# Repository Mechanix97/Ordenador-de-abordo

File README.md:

# Motorcycle On-Board Computer

A digital instrument cluster for a **Zanella RX 150** motorcycle that replaces the original analog
gauges. It measures **speed, engine RPM, fuel level and GPS position** and shows them on two OLED
displays, together with two LED bar graphs that can be read at a glance while riding.

Built on an STM32F103 "Blue Pill" with the STM32Cube HAL, on two home-made PCBs (toner transfer)
designed in KiCad to fit inside the original dashboard housing.

> Final project for *Seminario de Sistemas Embebidos*, Facultad de Ingeniería, Universidad de Buenos
> Aires (FIUBA), developed between November 2020 and March 2021. The project is being revived:
> see the [open issues](https://github.com/Mechanix97/Ordenador-de-abordo/issues) for the roadmap.

## Features

| Measurement | How it works | Status |
|---|---|---|
| Speed | Wheel switch → external interrupt, pulse counter | Shows raw pulse count ([#5](../../issues/5)) |
| Engine RPM | Rectified ignition signal → RC filter + Zener → ADC | Raw ADC value, uncalibrated ([#6](../../issues/6)) |
| Fuel level | Tank float sender (8–100 Ω) in a resistive divider → ADC | Raw ADC value ([#6](../../issues/6)) |
| GPS position, date, time | u-blox NEO-6M over UART + DMA, `$GPRMC` parsing | Working, accuracy < 10 m; known parser bugs ([#1](../../issues/1)–[#3](../../issues/3)) |
| LED bar graphs | 2 × LM3915 driven by filtered PWM, 10 LEDs each | Hardware works; firmware keeps them off |
| Push button | External interrupt | Counter only ([#7](../../issues/7)) |
| Bluetooth | HC-05 on USART1 | Used for debug output |

Display layout:

- **SH1106 (1.3")**: `VEL` (speed), `RPM`, `GAS` (fuel).
- **SSD1306 (0.96")**: `BUT` (button counter), `LAT`, `LON`, `DAT` (date), `TIME` (UTC-3).

## Hardware

### Components

| Component | Part | Interface |
|---|---|---|
| Microcontroller | STM32F103 "Blue Pill" (Cortex-M3, 72 MHz) | — |
| Display 1 | SH1106 128×64 OLED, 1.3" (I2C address `0x78`) | I2C1 |
| Display 2 | SSD1306 128×64 OLED, 0.96" (I2C address `0x7A`) | I2C1 |
| LED bar graphs | 2 × LM3915 + 20 LEDs | TIM2 PWM |
| GPS | u-blox NEO-6M module | USART3, 9600 baud |
| Bluetooth | HC-05 module | USART1, 9600 baud |

The project targets the `STM32F103CBTx` (128 KB flash). The firmware is about 24 KB, so it also fits
the more common STM32F103C8 (64 KB) found on most Blue Pill boards.

### Pinout

| Pin | Function | Peripheral |
|---|---|---|
| PA0 | Push button | EXTI0, rising edge, pull-up |
| PA1 | LED bar graph 2 | TIM2_CH2 PWM |
| PA2 | LED bar graph 1 | TIM2_CH3 PWM |
| PA6 | Engine RPM | ADC1_IN6 |
| PA7 | Fuel level | ADC2_IN7 |
| PA8 | Wheel-speed sensor | EXTI8, rising edge, pull-down |
| PA9 / PA10 | HC-05 Bluetooth TX / RX | USART1 |
| PB8 / PB9 | OLED SCL / SDA | I2C1 (remapped), 400 kHz |
| PB10 / PB11 | GPS TX / RX | USART3, RX via DMA |
| PA13 / PA14 | SWDIO / SWCLK | Debug |

The full configuration lives in [`Ordenador-abordo.ioc`](Ordenador-abordo.ioc) (STM32CubeMX).

### Sensor interfaces

| Fuel level | Engine RPM |
|---|---|
|  |  |
| The float sender goes from 100 Ω (reserve) to 8 Ω (full). With a 100 Ω pull-up the ADC reads roughly 100–2048 out of 4095. | The ignition signal is rectified, divided and filtered; a 5.5 V Zener protects the ADC pin from ignition spikes. The reading grows with RPM but is not calibrated yet. |

The speed sensor is a simple switch that closes once per wheel revolution.

### PCBs

Two boards, designed in KiCad 5.1 ([`Kicad/`](Kicad)) and made at home by toner transfer.

| Control board (100 × 50 mm) | Display board |
|---|---|
|  |  |
| Blue Pill carrier, Wago terminal blocks for the bike harness, signal conditioning, headers for the GPS and Bluetooth modules. | Shaped to fit the original gauge housing: two arcs of 10 LEDs driven by LM3915s, and headers for both OLED displays. |

> The `.sch` schematic files are empty; only the PCB layouts exist. Rebuilding the schematics is
> tracked in [#15](../../issues/15).

## Building

### Requirements

- [Arm GNU Toolchain](https://developer.arm.com/downloads/-/arm-gnu-toolchain-downloads) (`arm-none-eabi-gcc`)
- GNU Make
- [stlink-tools](https://github.com/stlink-org/stlink) (`st-flash`) and an ST-Link V2 for flashing

**Ubuntu / Debian**

```sh
sudo apt-get install build-essential gcc-arm-none-eabi libnewlib-arm-none-eabi stlink-tools
```

**Windows**: install [STM32CubeCLT](https://www.st.com/en/development-tools/stm32cubeclt.html) (includes
the toolchain) and GNU Make (e.g. `choco install make`). If the toolchain is not on `PATH`, pass it
explicitly: `make GCC_PATH="C:/ST/STM32CubeCLT_x.y.z/GNU-tools-for-STM32/bin"`.

### Commands

```sh
make all     # build build/Ordenador-abordo.{elf,hex,bin}
make clean   # remove build/
make erase   # erase the MCU flash
make flash   # write build/Ordenador-abordo.bin at 0x08000000
```

Connect the ST-Link to the SWD header of the Blue Pill (3.3V, SWDIO, SWCLK, GND).

Every push and pull request is built by [GitHub Actions](.github/workflows/build.yml); the
`.elf`/`.hex`/`.bin` files can be downloaded from the run's artifacts.

## Repository layout

```
Core/            Application code (app.c, gps.c, rpm.c, gas.c), OLED drivers, CubeMX-generated init code
Drivers/         STM32F1 HAL and CMSIS (vendor code, do not edit)
Kicad/           PCB designs: Placa-control (control board) and Placa-pantallas (display board)
docs/images/     Images used in this README
Makefile         Build script (generated by CubeMX, extended with flash/erase targets)
Ordenador-abordo.ioc   STM32CubeMX project
AGENTS.md        Guidelines for AI coding agents working on this repo
```

## Roadmap

Planned improvements are tracked as [GitHub issues](https://github.com/Mechanix97/Ordenador-de-abordo/issues), including:

- Robust GPS reception and NMEA parsing, timezone fixes ([#1](../../issues/1)–[#4](../../issues/4))
- Real speed in km/h, odometer and trip meter ([#5](../../issues/5))
- Calibrated RPM and fuel readings, driving the LED bar graphs ([#6](../../issues/6))
- Watchdog and robustness for an automotive environment ([#11](../../issues/11))
- Host-side unit tests ([#16](../../issues/16)) and KiCad schematics, Gerbers and BOM ([#15](../../issues/15))
- A 3D-printed enclosure and GPS navigation features

## License

No license has been chosen yet ([#18](../../issues/18)). Note that the OLED drivers in `Core/` are
GPL-3.0 and the ST HAL/CMSIS in `Drivers/` are BSD-3-Clause / Apache-2.0.

## Author

Lucas Alexis Rack ([@Mechanix97](https://github.com/Mechanix97))

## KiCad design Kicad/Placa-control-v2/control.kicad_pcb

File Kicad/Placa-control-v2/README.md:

# Control board v2

Redesign of the control board (`Kicad/Placa-control`) focused on **not destroying the electronics
again**. The v1 board was killed through the RPM input, which was wired straight from the ignition
coil to the microcontroller.

- **Single-sided, through-hole only**, for home etching (toner transfer). 3 wire jumpers.
- Same outline as v1 (100 × 50 mm with the chamfered corner), so it fits the original dashboard housing.
- KiCad 10 project with a **complete schematic**: v1 only had a PCB.
- ERC and DRC are clean and run in CI on every change (`.github/workflows/kicad.yml`).

| | |
|---|---|
| Schematic | [docs/control-v2-schematic.pdf](docs/control-v2-schematic.pdf) |
| Layout (copper + silkscreen, seen from the component side) | [docs/control-v2-layout.svg](docs/control-v2-layout.svg) |
| Gerbers, drill file, BOM, toner-transfer PDF | CI artifact `control-board-fab-<sha>` of the **KiCad** workflow |

## Why v1 failed

1. **RPM input.** Coil → diode → 100 kΩ → 100 kΩ ∥ 100 nF ∥ **5.5 V Zener** → PA6.
   - PA6 is a 3.3 V pin, not 5 V tolerant: its absolute maximum is about 3.6 V. The MCU's internal
     protection diodes conducted before the Zener did, and every spark injected current into the
     3.3 V rail.
   - That rail also feeds the displays, the GPS and the Bluetooth module, which is why everything
     died at once.
   - A single small 0204 resistor also had to stand hundreds of volts.
2. **Footprint bug.** One row of the v1 Blue Pill footprint was numbered in reverse. 5 V, GND and the
   RPM signal landed on the wrong module pins and had to be fixed with wires.
3. **No protection on the 12 V input or on the sensor inputs**, and no protection against a
   failing or mis-adjusted regulator preset.

## What's new

| Block | v2 circuit | Protects against |
|---|---|---|
| RPM input | 1N4007 → 3 × 47 kΩ in series → **PC817 optocoupler** (+ 1N4148 across the LED). Output to PA6 through 1 kΩ, 1 nF filter, internal pull-up | Coil voltage never reaches the MCU (galvanic isolation through the opto); negative pulses; resistor over-voltage |
| | 2.5 mm clearance from the coil nets to everything else (custom DRC rule, applied to the GND pour too); empty connector pins on both sides of the coil input | Arcing and creepage |
| 12 V input | PTC fuse 0.5 A / 60 V → 1N5819 (reverse polarity) → P6KE22A TVS + 47 µF | Shorts, reversed battery, load-dump spikes (clamped to ~31 V, below the 40 V limit of LM2596 modules) |
| 5 V rail | PTC fuse 0.5 A → **1N5340B 6 V / 5 W Zener crowbar** + 100 µF | A failed or mis-adjusted regulator preset: the Zener conducts and the PTC trips instead of 12 V reaching the modules |
| Wheel speed (PA8) | 4.7 kΩ pull-up to 5 V (switch to GND), 10 kΩ series, 100 nF, 4.7 V Zener | Shorts to 12 V, spikes, contact bounce |
| Fuel level (PA7) | 5 V → 1N4148 → 150 Ω divider with the sender, 10 kΩ series, 100 nF, 3.3 V Zener | Sender wire touching 12 V (no back-feed into 5 V), spikes |
| Button (PA0) | 1 kΩ series + 100 nF (internal pull-up) | ESD, bounce |
| LED bars | 10 kΩ / 8.2 kΩ / 1 µF PWM filters (full scale ≈ 1.5 V for the LM3915) | — |

## Connectors

| Ref | Type | Pin 1 → n |
|---|---|---|
| J1 POWER | Wago 734-135 (5 pins) | 1 +12 V (after the ignition switch), 2 GND, 3 to regulator IN+, 4 regulator GND (IN− / OUT−), 5 from regulator OUT+ |
| J2 SENSORS | Wago **734-136 (6 pins)** | 1 fuel sender, 2 *empty*, 3 **ignition coil**, 4 *empty*, 5 wheel switch, 6 GND |
| J3 DISPLAYS | 1×4 socket | 1 GND, 2 +5 V, 3 SDA (PB9), 4 SCL (PB8) |
| J7 LED BARS | 1×3 socket | 1 BAR1 (PA2), 2 GND, 3 BAR2 (PA1) |
| J4 GPS | 1×4 socket | 1 GND, 2 TX → PB11, 3 RX ← PB10, 4 VCC (+5 V) |
| J5 BLUETOOTH | 1×6 socket | 1 EN (n.c.), 2 VCC (+5 V), 3 GND, 4 TXD → PA10, 5 RXD ← PA9, 6 STATE (n.c.) |
| J6 BUTTON | 1×2 socket | 1 button (to PA0), 2 GND |

- **Display board wiring changes.** The old 6-wire cable is replaced by J3 (OLEDs) and J7 (LM3915
  inputs), so the display board needs rewiring.
- **The RPM wire goes to the coil primary**, the low-voltage terminal driven by the CDI. Never connect
  it to the spark plug lead.
- **The external step-down module:** IN+ on J1-3, OUT+ on J1-5, and its common GND on J1-4.
  **Adjust it to 5.0 V before connecting it.**

## Wire jumpers

The board is single-sided, so three crossings are made with insulated wire on the component side.
They are drawn on the silkscreen as `W1`–`W3`:

| Ref | Net | Where |
|---|---|---|
| W1 | +5V | Long diagonal on the left of the Blue Pill (feeds the module, displays and Bluetooth) |
| W2 | GND | Short, above the left end of the Blue Pill |
| W3 | GND | **Under the Blue Pill** (between the two socket rows): install it before the sockets |

## Assembly notes

- Parts under the Blue Pill must be lower than ~7 mm. Only W3 is there; use standard 8.5 mm female headers.
- The `BluePill_Socketed` footprint prints the pin names next to each pad. **Compare them with the
  labels on your module before soldering the headers.** USB goes towards the right edge, SWD towards
  the left.
- R1–R3: use 1/4 W metal-film resistors (≥ 250 V). The PTCs are 5.1 mm radial, rated 60 V (RXEF050,
  MF-R050 or similar).
- Wago 734 pins are 1 mm square: drill the J1/J2 holes with 1.3–1.5 mm.
- A conformal coating (or clear nail polish) over the RPM area improves creepage in a damp environment.

## Bring-up checklist

1. Without the Blue Pill or any module plugged in, power J1-1 from a bench supply (12 V,
   current-limited to ~200 mA). Check about 11.6 V on J1-3 (regulator input).
2. Connect the step-down module and check **5.0 V** on J3-2 / J4-4 / J5-2.
3. Plug the Blue Pill, then the displays, GPS and Bluetooth one at a time.
4. On the bike, check the RPM input with the engine at idle: PA6 should show clean low pulses.
   A scope is ideal.

## Firmware

The pins are the same as v1, but some inputs work differently. The firmware and the `.ioc` are
already set up for this board:

| Pin | Board v2 behaviour | Firmware |
|---|---|---|
| PA6 (RPM) | Digital pulse from the optocoupler, low on every spark | TIM3_CH1 input capture (100 kHz, falling edge, internal pull-up, digital filter). `rpm.c` ignores edges closer than 2 ms (ignition ringing) and reports 0 after 500 ms without sparks. Set `RPM_SPARKS_PER_2_REV` in `rpm.h` for your CDI. |
| PA7 (fuel) | About 0.2 V (full) … 1.7 V (reserve), 10 kΩ source impedance | ADC2 with 239.5-cycle sampling. Calibrate `GAS_RAW_FULL` / `GAS_RAW_RESERVE` in `gas.h` with the raw value shown on the display. |
| PA8 (speed) | External pull-up, the switch pulls it low | No internal pull. |
| PA0 (button) | Internal pull-up | Unchanged. |

## Design rules

- Net classes are defined in `control.kicad_pro`:
  - **Default:** 0.6 mm tracks, 0.4 mm clearance.
  - **Power:** 1.0 mm tracks.
  - **HV:** the coil nets, 0.8 mm tracks.
- The 2.5 mm HV clearance is a custom rule in `control.kicad_dru`. It excludes the empty connector pins.
- The Blue Pill footprint declares its internally connected pins (GND 19/20/22, 3V3 18/21) as pad
  groups, so the DRC knows the module ties them together.
- The GND pour is part of the design. After editing, refill zones (`B`) before running the DRC.

## Fabrication

- **Toner transfer.** Print `control-copper-bottom.pdf` from the CI artifact **at 100 % scale and
  without mirroring**, and transfer it face-down onto the copper. Check the orientation with the
  Blue Pill footprint before etching.
- **Ordering the board.** The CI artifact also contains single-sided Gerbers and the Excellon drill file.

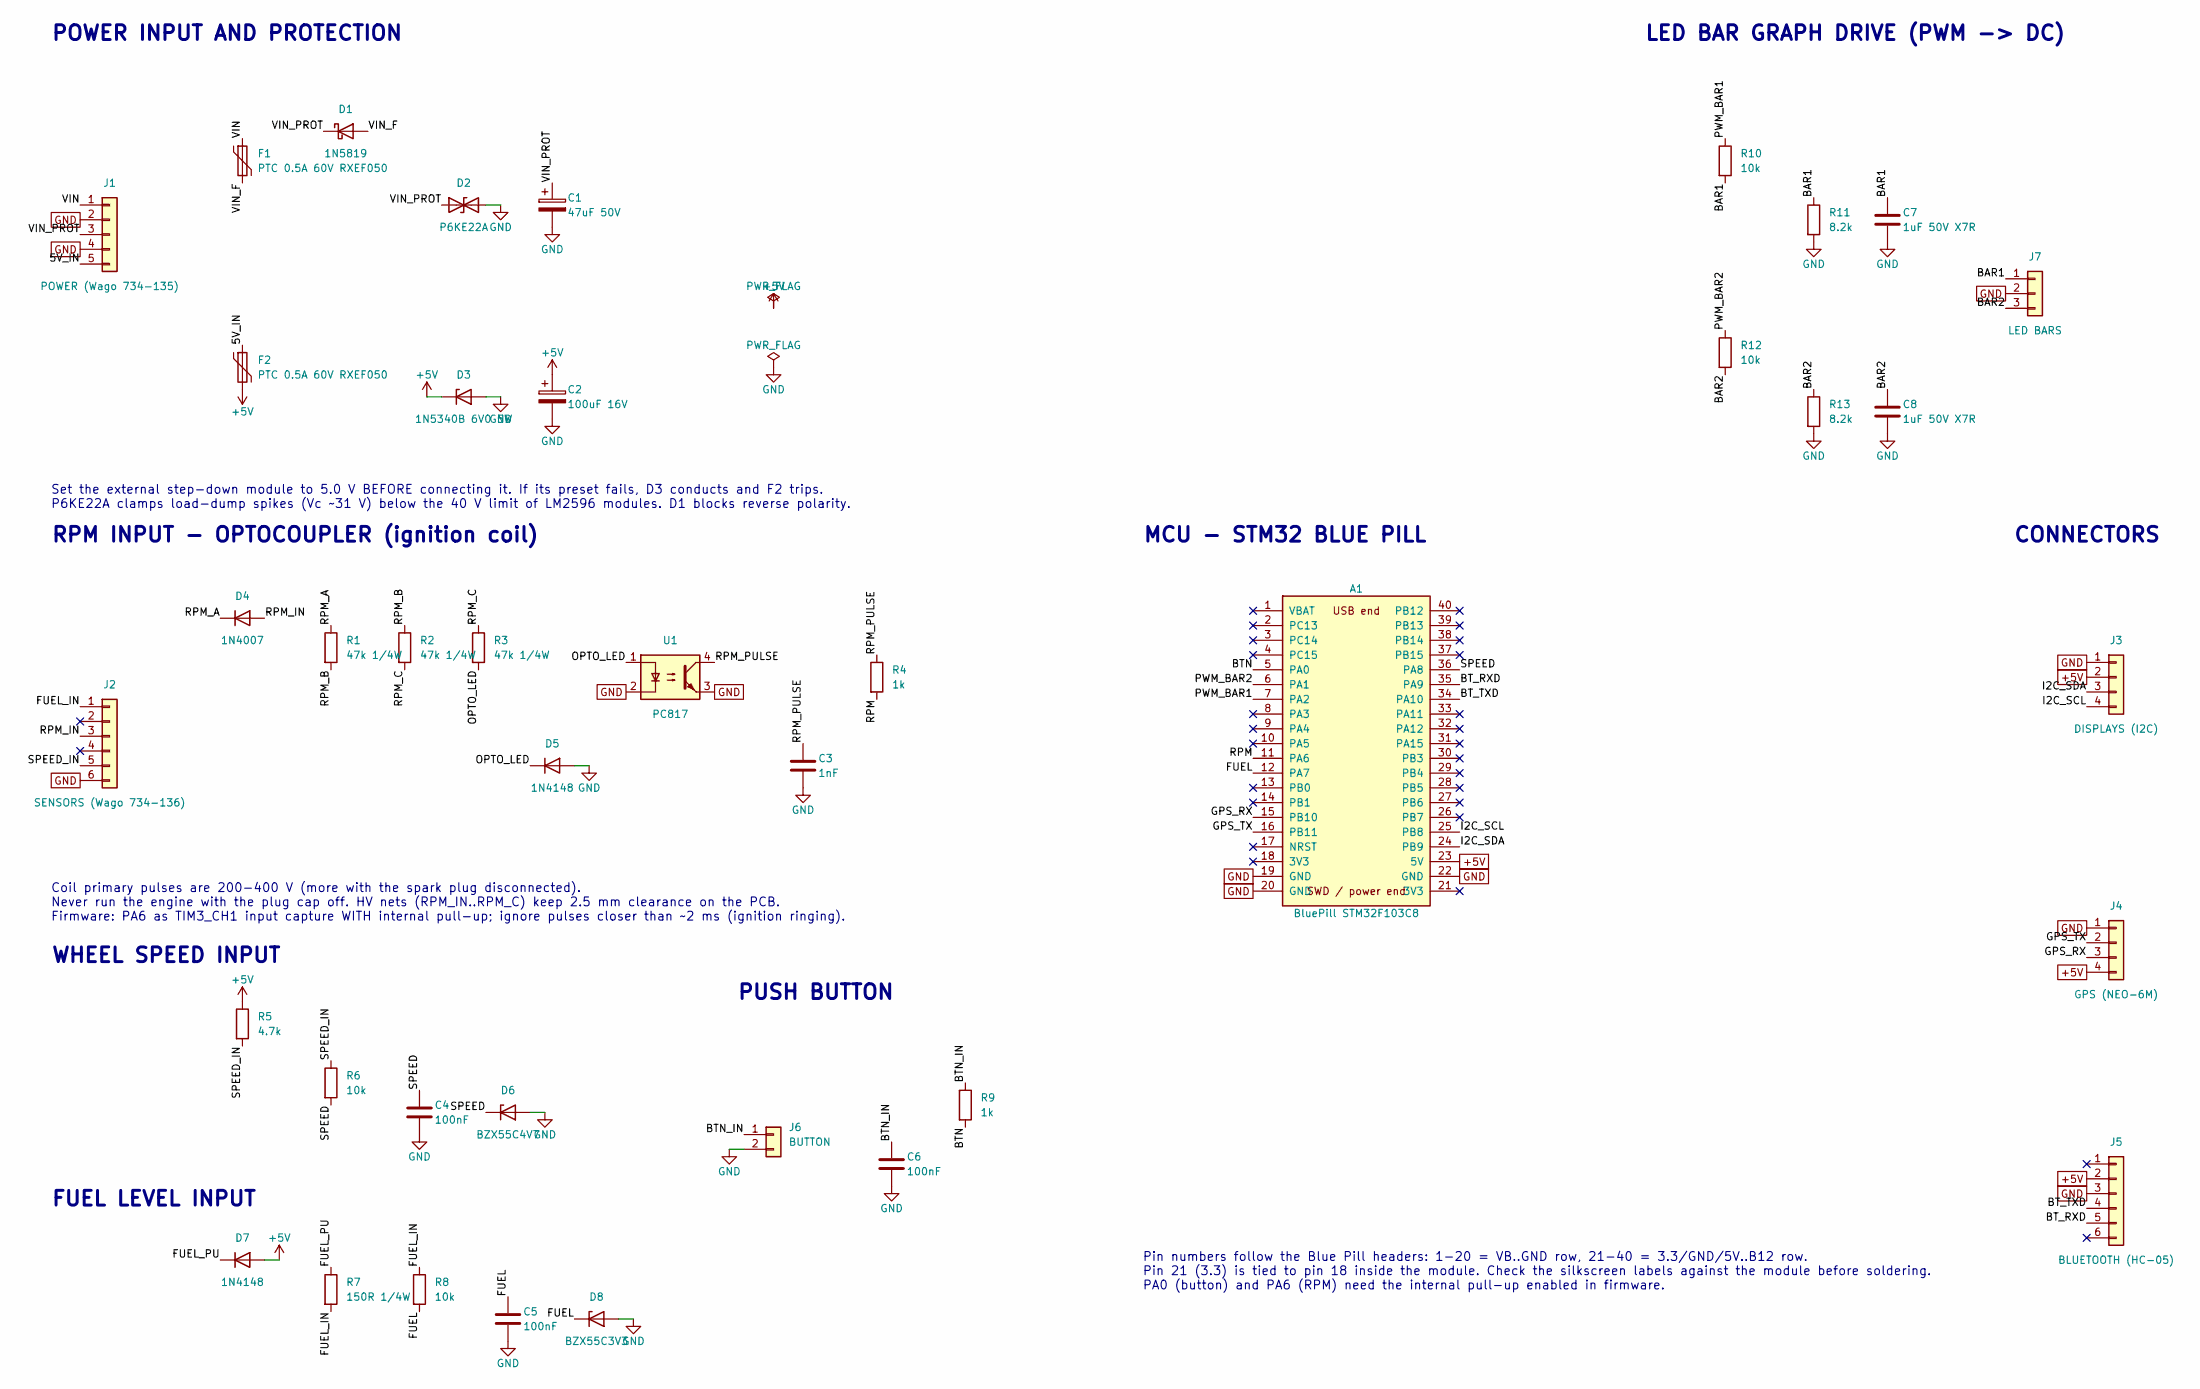
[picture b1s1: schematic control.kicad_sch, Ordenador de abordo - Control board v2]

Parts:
A1: BluePill STM32F103C8; BluePill_Socketed
C1: 47uF 50V; CP_Radial_D6.3mm_P2.50mm
C2: 100uF 16V; CP_Radial_D6.3mm_P2.50mm
C3: 1nF; C_Disc_D3.0mm_W1.6mm_P2.50mm
C4, C5, C6: 100nF; C_Disc_D3.0mm_W1.6mm_P2.50mm
C7, C8: 1uF 50V X7R; C_Disc_D3.0mm_W1.6mm_P2.50mm
D1: 1N5819; D_DO-41_SOD81_P10.16mm_Horizontal
D2: P6KE22A; D_DO-15_P10.16mm_Horizontal
D3: 1N5340B 6V0 5W; D_DO-201AE_P5.08mm_Vertical_AnodeUp
D4: 1N4007; D_DO-41_SOD81_P10.16mm_Horizontal
D5, D7: 1N4148; D_DO-35_SOD27_P2.54mm_Vertical_AnodeUp
D6: BZX55C4V7; D_DO-35_SOD27_P2.54mm_Vertical_AnodeUp
D8: BZX55C3V3; D_DO-35_SOD27_P2.54mm_Vertical_AnodeUp
F1, F2: PTC 0.5A 60V RXEF050; Fuse_Bourns_MF-RHT050
J1: POWER (Wago 734-135); Wago_734-135_1x05_P3.50mm_Vertical
J2: SENSORS (Wago 734-136); Wago_734-136_1x06_P3.50mm_Vertical
J3: DISPLAYS (I2C); PinSocket_1x04_P2.54mm_Vertical
J4: GPS (NEO-6M); PinSocket_1x04_P2.54mm_Vertical
J5: BLUETOOTH (HC-05); PinSocket_1x06_P2.54mm_Vertical
J6: BUTTON; PinSocket_1x02_P2.54mm_Vertical
J7: LED BARS; PinSocket_1x03_P2.54mm_Vertical
R1, R2, R3: 47k 1/4W; R_Axial_DIN0207_L6.3mm_D2.5mm_P10.16mm_Horizontal
R4, R9: 1k; R_Axial_DIN0207_L6.3mm_D2.5mm_P2.54mm_Vertical
R5: 4.7k; R_Axial_DIN0207_L6.3mm_D2.5mm_P2.54mm_Vertical
R6, R8, R10, R12: 10k; R_Axial_DIN0207_L6.3mm_D2.5mm_P2.54mm_Vertical
R7: 150R 1/4W; R_Axial_DIN0207_L6.3mm_D2.5mm_P2.54mm_Vertical
R11, R13: 8.2k; R_Axial_DIN0207_L6.3mm_D2.5mm_P2.54mm_Vertical
U1: PC817; DIP-4_W7.62mm

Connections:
+5V: A1.23 (5V), C2.1, D3.1 (K), D7.2 (A), F2.2, J3.2, J4.4, J5.2, R5.1; also elsewhere on the board
/5V_IN: F2.1, J1.5
/BAR1: C7.1, J7.1, R10.2, R11.1
/BAR2: C8.1, J7.3, R12.2, R13.1
/BTN: A1.5 (PA0), R9.2
/BTN_IN: C6.1, J6.1, R9.1
/BT_RXD: A1.35 (PA9), J5.5
/BT_TXD: A1.34 (PA10), J5.4
/FUEL: A1.12 (PA7), C5.1, D8.1 (K), R8.2
/FUEL_IN: J2.1, R7.2, R8.1
/FUEL_PU: D7.1 (K), R7.1
/GPS_RX: A1.15 (PB10), J4.3
/GPS_TX: A1.16 (PB11), J4.2
/I2C_SCL: A1.25 (PB8), J3.4
/I2C_SDA: A1.24 (PB9), J3.3
/OPTO_LED: D5.1 (K), R3.2, U1.1
/PWM_BAR1: A1.7 (PA2), R10.1
/PWM_BAR2: A1.6 (PA1), R12.1
/RPM: A1.11 (PA6), R4.2
/RPM_A: D4.1 (K), R1.1
/RPM_B: R1.2, R2.1
/RPM_C: R2.2, R3.1
/RPM_IN: D4.2 (A), J2.3
/RPM_PULSE: C3.1, R4.1, U1.4
/SPEED: A1.36 (PA8), C4.1, D6.1 (K), R6.2
/SPEED_IN: J2.5, R5.2, R6.1
/VIN: F1.1, J1.1
/VIN_F: D1.2 (A), F1.2
/VIN_PROT: C1.1, D1.1 (K), D2.1 (A1), J1.3
GND: A1.19 (GND), A1.20 (GND), A1.22 (GND), C1.2, C2.2, C3.2, C4.2, C5.2, C6.2, C7.2, C8.2, D2.2 (A2), D3.2 (A), D5.2 (A), D6.2 (A), D8.2 (A), J1.2, J1.4, J2.6, J3.1, J4.1, J5.3, J6.2, J7.2, R11.2, R13.2, U1.2, U1.3; also elsewhere on the board

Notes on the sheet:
POWER INPUT AND PROTECTION
RPM INPUT - OPTOCOUPLER (ignition coil)
WHEEL SPEED INPUT
FUEL LEVEL INPUT
PUSH BUTTON
MCU - STM32 BLUE PILL
LED BAR GRAPH DRIVE (PWM -> DC)
CONNECTORS
Set the external step-down module to 5.0 V BEFORE connecting it. If its preset fails, D3 conducts and F2 trips. P6KE22A clamps load-dump spikes (Vc ~31 V) below the 40 V limit of LM2596 modules. D1 blocks reverse polarity.
Coil primary pulses are 200-400 V (more with the spark plug disconnected). Never run the engine with the plug cap off. HV nets (RPM_IN..RPM_C) keep 2.5 mm clearance on the PCB. Firmware: PA6 as TIM3_CH1 input capture WITH internal pull-up; ignore pulses closer than ~2 ms (ignition ringing).
Pin numbers follow the Blue Pill headers: 1-20 = VB..GND row, 21-40 = 3.3/GND/5V..B12 row. Pin 21 (3.3) is tied to pin 18 inside the module. Check the silkscreen labels against the module before soldering. PA0 (button) and PA6 (RPM) need the internal pull-up enabled in firmware.

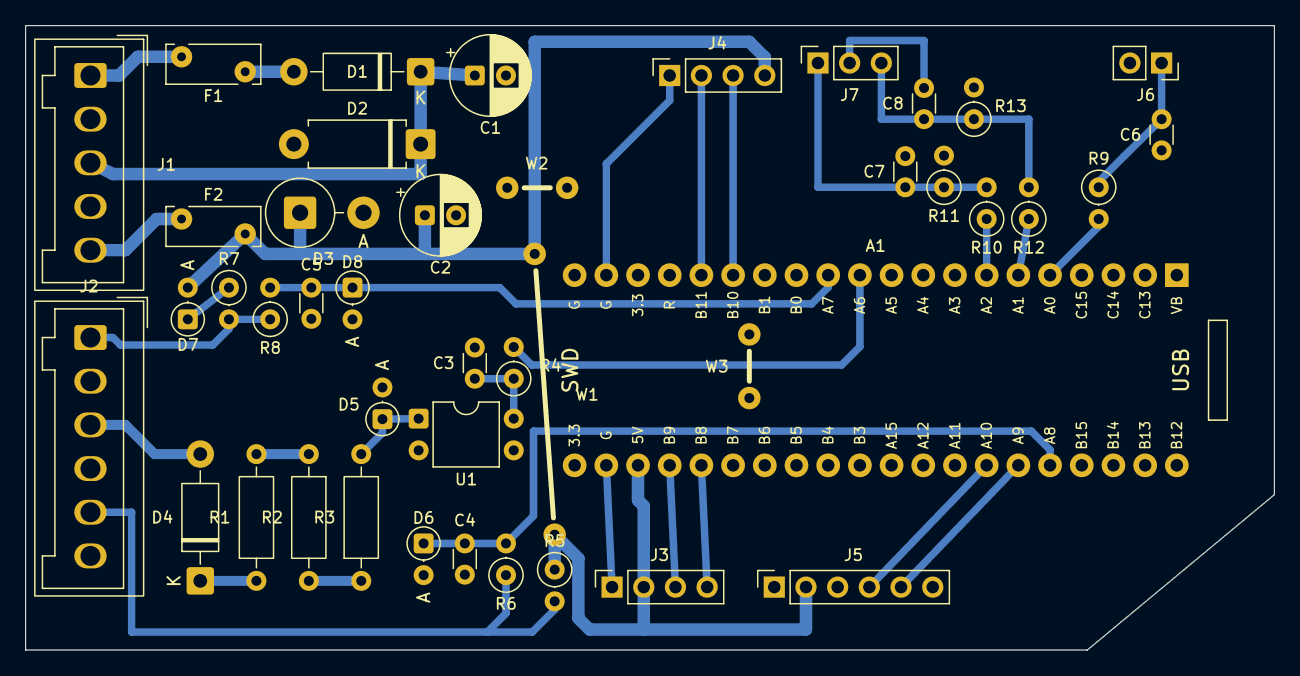
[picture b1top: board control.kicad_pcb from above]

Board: 2 copper layers, 100.1 x 50.0 mm, 43 parts (0 on the bottom side), 30 nets.

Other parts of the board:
W1: Wire jumper 23 mm; WireJumper
W2, W3: Wire jumper 5 mm; WireJumper

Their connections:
+5V: W1.1; also elsewhere on the board
GND: W2.1, W3.1; also elsewhere on the board

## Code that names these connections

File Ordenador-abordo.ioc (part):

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Mcu.Name=STM32F103C(8-B)Tx
Mcu.Package=LQFP48
Mcu.UserName=STM32F103CBTx
PA0-WKUP.GPIOParameters=GPIO_PuPd,GPIO_Label,GPIO_ModeDefaultEXTI
PA0-WKUP.GPIO_Label=Button
PA0-WKUP.GPIO_ModeDefaultEXTI=GPIO_MODE_IT_RISING
PA0-WKUP.GPIO_PuPd=GPIO_PULLUP
PA0-WKUP.Signal=GPXTI0
PA1.Signal=S_TIM2_CH2
PA10.Mode=Asynchronous
PA10.Signal=USART1_RX
PA13.Mode=Serial_Wire
PA13.Signal=SYS_JTMS-SWDIO
PA14.Mode=Serial_Wire
PA14.Signal=SYS_JTCK-SWCLK
PA2.Signal=S_TIM2_CH3
PA6.GPIOParameters=GPIO_PuPd
PA6.GPIO_PuPd=GPIO_PULLUP
PA6.Signal=S_TIM3_CH1
PA7.Signal=ADCx_IN7
PA8.GPIOParameters=GPIO_PuPd,GPIO_Label,GPIO_ModeDefaultEXTI
PA8.GPIO_Label=speedometer
PA8.GPIO_ModeDefaultEXTI=GPIO_MODE_IT_RISING
PA8.GPIO_PuPd=GPIO_NOPULL
PA8.Signal=GPXTI8
PA9.Mode=Asynchronous
PA9.Signal=USART1_TX
PB10.Mode=Asynchronous
PB10.Signal=USART3_TX
PB11.Mode=Asynchronous
PB11.Signal=USART3_RX
PB8.Mode=I2C
PB8.Signal=I2C1_SCL
PB9.Mode=I2C
PB9.Signal=I2C1_SDA
PD0-OSC_IN.Mode=HSE-External-Oscillator
PD0-OSC_IN.Signal=RCC_OSC_IN
PD1-OSC_OUT.Mode=HSE-External-Oscillator
PD1-OSC_OUT.Signal=RCC_OSC_OUT
RCC.SYSCLKFreq_VALUE=72000000
RCC.SYSCLKSource=RCC_SYSCLKSOURCE_PLLCLK
board=custom

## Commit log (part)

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2021-02-16 documentos
2021-02-16 Readme
2021-02-16 git ignore
2021-02-16 fix ignore
2021-02-16 fix readme
2021-02-17 Cambio de template
2021-02-17 2 pantallas
2021-02-21 Ext int y BLUTU
2021-02-22 loop y setup
2021-02-23 Button
2021-03-16 agrego kicad
2021-03-16 fix anterior
2021-03-23 Kicad mejorado
2021-03-30 final
2021-03-31 Kicad pantallas
